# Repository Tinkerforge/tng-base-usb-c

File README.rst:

TNG Base USB C
==============

**This TNG module is currently in development.**

This repository contains the firmware source code and the hardware design
files. The documentation generator configs can be found at
https://github.com/Tinkerforge/generators

Repository Content
------------------

software/:
 * examples/: Examples for all supported languages
 * build/: Compiled files
 * src/: Source code of firmware
 * Makefile: Makefile to build project

hardware/:
 * Contains KiCad project files and additionally schematics as PDF

datasheets/:
 * Contains datasheets for sensors and complex ICs that are used

Hardware
--------

The hardware is designed with the open source EDA Suite KiCad
(http://www.kicad.org). Before you are able to open the files,
you have to install the Tinkerforge kicad-libraries
(https://github.com/Tinkerforge/kicad-libraries). You can either clone
them directly in hardware/ or clone them in a separate folder and
symlink them into hardware/
(ln -s kicad_path/kicad-libraries project_path/hardware). After that you
can open the .pro file in hardware/ with KiCad and from there view and
modify the schematics and the PCB layout.

Software
--------

If you want to do your own Brick/Bricklet firmware development we highly
recommend that you use our build environment setup script and read the
tutorial (https://www.tinkerforge.com/en/doc/Tutorials/Tutorial_Build_Environment/Tutorial.html).

To compile the C code we recommend you to install the newest GNU Arm Embedded
Toolchain (https://launchpad.net/gcc-arm-embedded/+download).
You also need to install bricklib2 (https://github.com/Tinkerforge/bricklib2).

You can either clone it directly in software/src/ or clone it in a
separate folder and symlink it into software/src/
(ln -s bricklib_path/bricklib2 project_path/software/src/). Finally make sure to
have CMake installed (http://www.cmake.org/cmake/resources/software.html).

After that you can build the firmware by invoking make in software/.
The firmware (.zbin) can then be found in software/build/ and uploaded
with brickv (click button "Flashing" on start screen).

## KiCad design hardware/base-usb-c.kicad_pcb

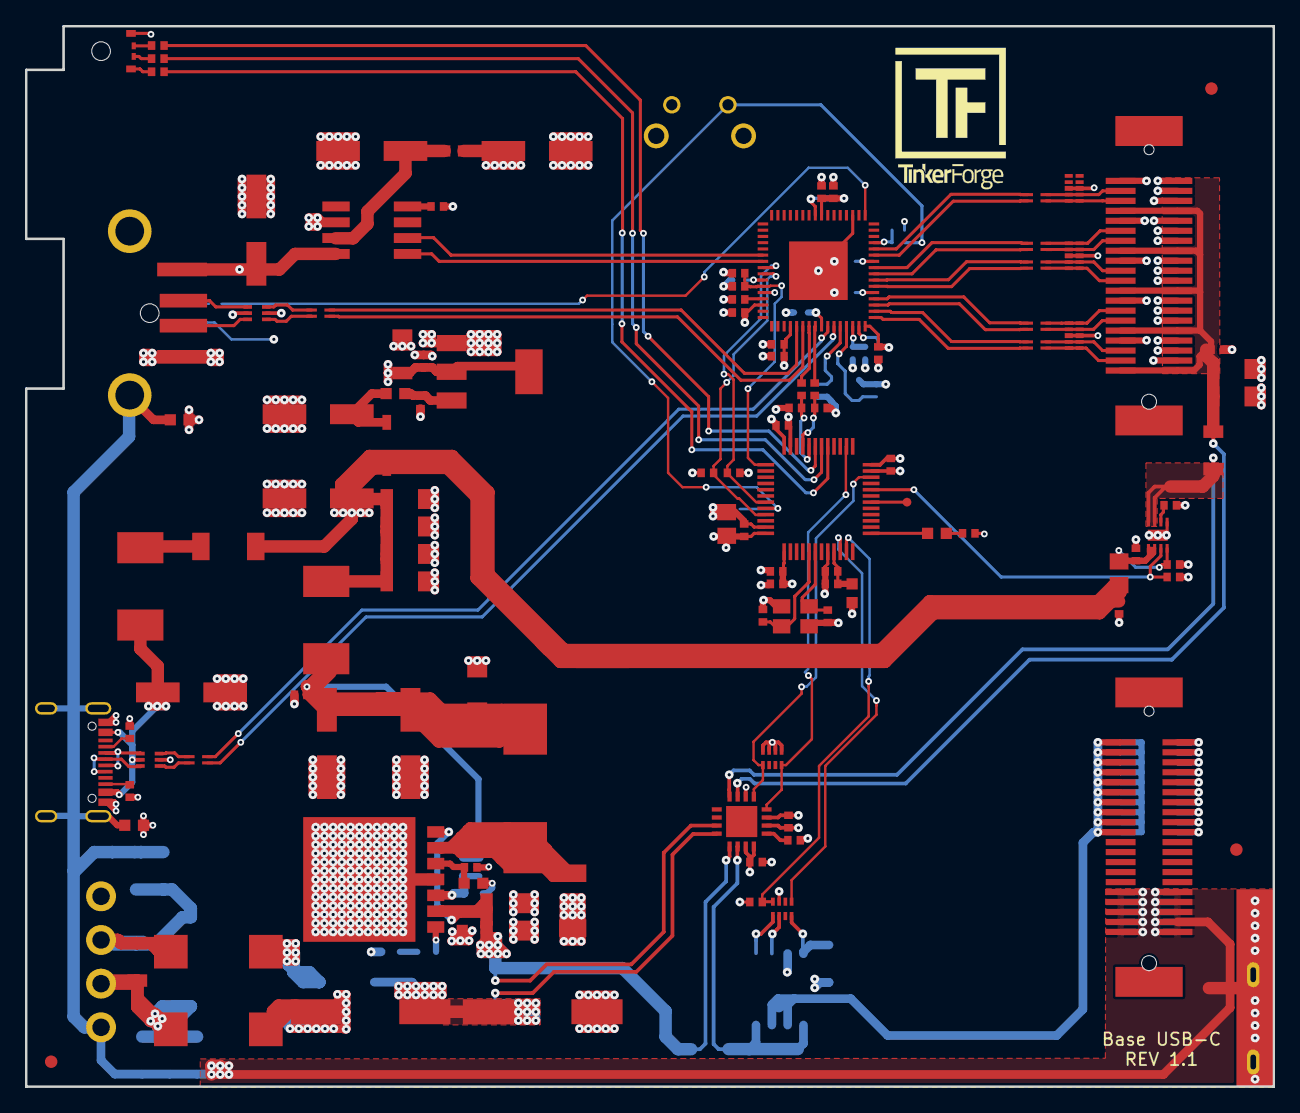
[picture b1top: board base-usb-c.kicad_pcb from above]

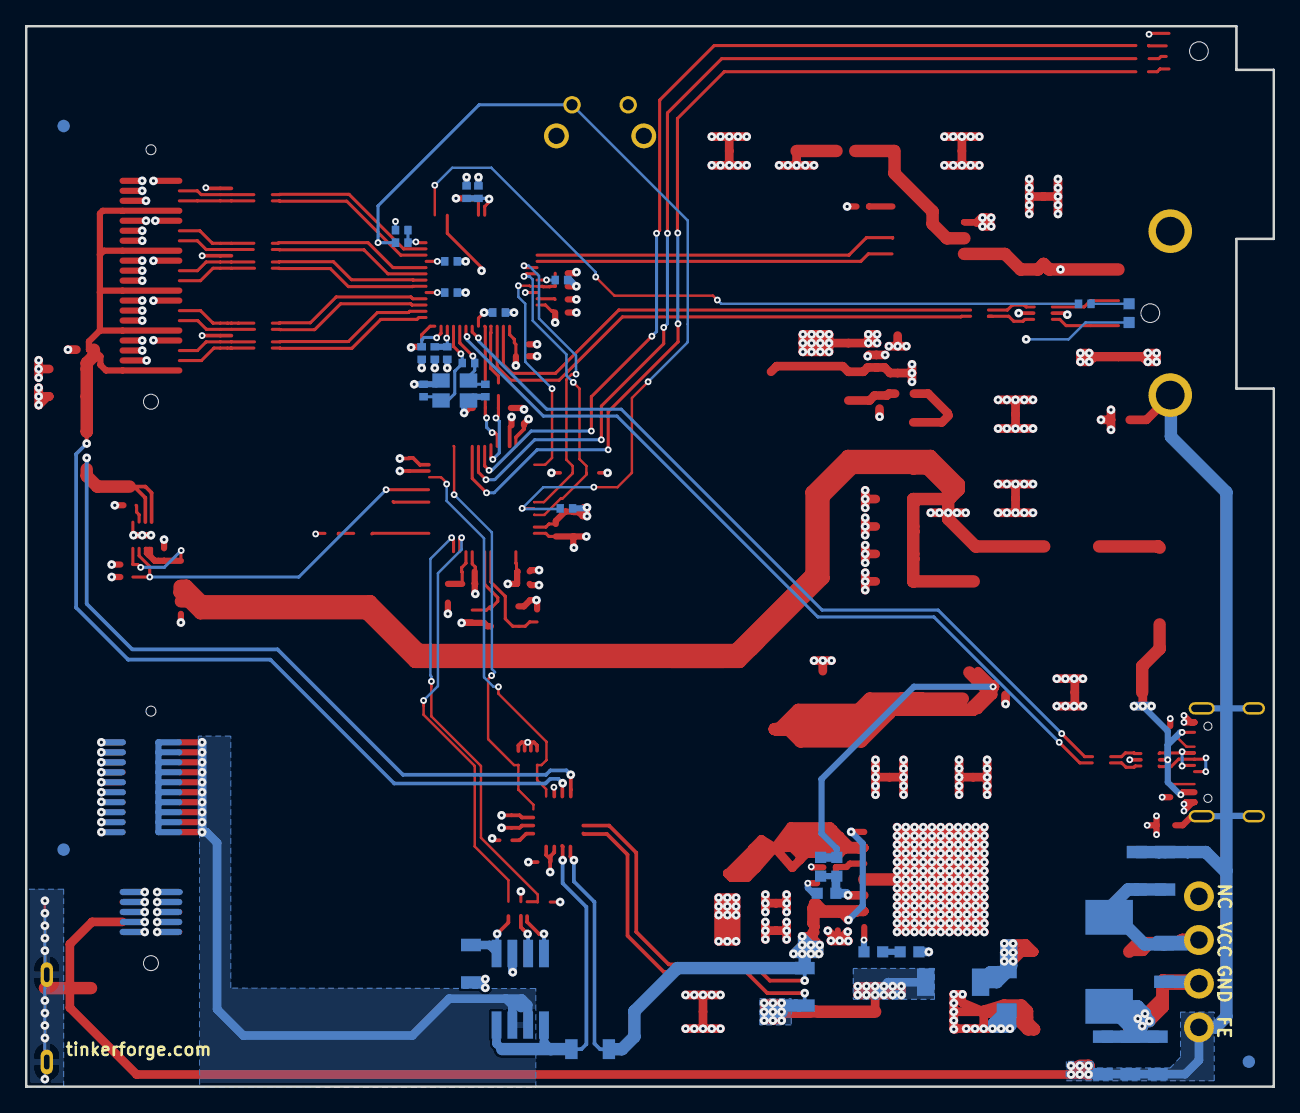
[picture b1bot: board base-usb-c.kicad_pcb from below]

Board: 4 copper layers, 100.0 x 85.0 mm, 157 parts (39 on the bottom side), 103 nets.

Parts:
C101, C102, C137, C138: 33pF; C0402F
C103, C105, C115, C119, C123, C124, C125, C126, C128, C134, C209, C226: 1uF; C0402F
C104, C106, C107, C110, C111, C112, C113, C114, C116, C118, C127, C129, C130, C131, C133, C214, C221, C222: 100nF; C0402F
C108, C109, C117, C141, C203, C216, C219, C220: 100uF; ELKO_63
C120, C140, C205: 100nF; C0603F
C121, C122: 47pF; C0402F
C132: DNP; C0402F
C135, C136, C201, C202, C215, C218, C223, C224, C225, C227: 10uF; C1206
C139: 10uF; C0805E
C204, C211: 10nF; C1206
C206, C207: 1nF 2kV; C1206
C208: 100pF; C0402F
C210: 4.7nF; C0603F
C212, C213: UWT1H221MNL1GS; ELKO_103
C217: DNP; C0603F
D101: LED green; LED-LP
D102: LED; D0603F
D201: 3.0SMI30CATR; SMC
D202, D205, D206: PMEG6045; SOD-128
D203: B0520LW-7-F; SOD-123
Fiducial_Mark: VAL**; Fiducial_Mark
Fiducial_Mark#2, Fiducial_Mark#3, Fiducial_Mark#4, Fiducial_Mark#5, Fiducial_Mark#6: VAL**; Fiducial_Mark
J101: USB-A; USB-A-SMT-8231
J102: USB-C; USB-C-2
J103: TNG-Power-TOP; TNG-40-TOP
J105: TNG-Data-TOP; TNG-40-TOP
L101, L201: INDUCTs; R0603F
L102, L103, L104, L105, L106, L107, L110: 744230900; WE-CNSW-0603
L108: FB; R0603F
L109: 742792040; R0805E
L111, L203: 10uH; SRP7030
L202: 22uH 74437368220; WE-LHMI
LED101: EASV3015RGBA0; LED-RGB-LP
P101: Debug; DEBUG_PAD
P102: PE; PE_Hook
P202: PWR IN; OQ_4P
R101, R105, R106, R107, R109, R111, R116, R117, R218: 10k; R0402F
R102: 100k; R0402F
R103: 1M; R0402F
R104, R108, R114, R121: 1k; R0402F
R110: 12k; R0402F
R112, R113: 22; R0402F
R115, R119: 0; R0402F
R118: 1k; R1206
R120: 56; R0402F
R122, R123: 5k1; R0402F
R204, R206, R207: VC1206K201R030; R1206
R208: 27k; R0603F
R209: 1M; R1206
R212: 20k; R0603F
R214: 47k; R0603F
R215: 8.2k; R0603F
R219, R220, R221: 0.02; R1206
RP102, RP201: 10k; 4X0402
SW101: BOOT; TACT-6MM-HOR
T201: 744272251; WE-SL5
U101: USB2517; QFN64-9x9mm-0.5mm_USB2517
U102: MIC2026-1YM; SO-8
U103, U108: 82400152; SOT563-SPEC
U104: STM32F070CBT6; LQFP48
U105, U106, U107: TPD4S010DQA
U110: TPS22975; WSON8-2x2
U112: VN7140AS; SO-8
U201: AZ1117EH; SOT-223
U203: BD90640HFP; BD906XX-C-HRP7
U204: PAC1933; QFN-16
X101: 24MHz; CRYSTAL_3225
X102: 8MHz; CRYSTAL_3225

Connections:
3V3: C110.1, C111.1, C112.1, C113.1, C114.1, C115.1, C116.1, C118.1, C119.1, C123.1, C127.1, C129.1, C130.1, C131.1, C139.1, C221.1, C222.1, C226.1, C227.1, D101.1, L108.1, LED101.1, R101.2, R102.2, R106.2, R111.2, R116.2, R117.2, R121.2, RP102.7, RP201.1, RP201.2, RP201.3, RP201.4, SW101.1, U101.5, U101.10, U101.24, U101.44, U101.46, U101.52, U101.57, U101.64, U104.1, U104.24, U104.36, U104.48, U201.2, U204.2, U204.6, U204.15, U204.16
5V_STACK_UP: C134.2, C135.2, C136.2, J105.7, J105.8, J105.15, J105.16, J105.23, J105.24, J105.31, J105.32, J105.39, J105.40, R221.2, U204.7
+5V: C108.1, C125.2, C218.1, C219.1, C223.1, C224.1, C225.1, D202.2, D203.1, L101.2, L109.1, L203.2
BOOT: R108.2, R114.2, SW101.2, U104.44
CTRL_USB_D+: C122.1, R112.2, U104.33
CTRL_USB_D-: C121.1, R113.2, U104.32
CUR1+: C212.1, C213.1, D205.2, R219.1, U204.12
CUR1-: C201.1, C202.1, C205.1, R219.2, R220.1, U203.2, U203.7, U204.11, U204.13
CUR2-: R220.2, U112.5, U112.8, U204.14
CUR3+: R221.1, U110.7, U110.8, U204.8
EXT_USB_D+: L102.1, U101.54
EXT_USB_D-: L102.4, U101.53
EXT_USB_D_F+: J101.3, U103.6
EXT_USB_D_F-: J101.2, U103.4
Earth: C120.1, C140.1, C206.2, C207.1, J101.SHD, J102.SHD, J103.31, J103.32, J103.33, J103.34, J103.35, J103.36, J103.37, J103.38, J103.39, J103.40, P102.1, P202.4, R206.2, R207.1, R209.1
GND: C101.2, C102.2, C103.2, C104.2, C105.2, C106.2, C107.2, C108.2, C109.2, C110.2, C111.2, C112.2, C113.2, C114.2, C115.2, C116.2, C117.2, C118.2, C119.2, C120.2, C121.2, C122.2, C123.2, C124.2, C125.1, C126.1, C127.2, C128.2, C129.2, C130.2, C131.2, C132.2, C133.2, C134.1, C135.1, C136.1, C137.1, C138.1, C139.2, C140.2, C141.2, C201.2, C202.2, C203.2, C205.2, C208.2, C209.2, C210.2, C211.2, C212.2, C213.2, C214.2, C215.2, C216.2, C218.2, C219.2, C220.2, C221.2, C222.2, C223.2, C224.2, C225.2, C226.2, C227.2, D206.1, J101.4, J102.6, J103.2, J103.4, J103.6, J103.8, J103.10, J103.12, J103.14, J103.16, J103.18, J103.20, J105.1, J105.2, J105.4, J105.6, J105.9, J105.10, J105.12, J105.14, J105.17, J105.18, J105.20, J105.22, J105.25, J105.26, J105.28, J105.30, J105.33, J105.34, J105.36, J105.38, R105.1, R107.2, R109.2, R110.1, R114.1, R118.1, R122.1, R123.1, R208.1, R215.1, R218.2, T201.3, U101.19, U101.EXP, U102.6, U103.2, U104.8, U104.23, U104.35, U104.47, U105.3, U105.8, U106.3, U106.8, U107.3, U107.8, U108.2, U110.5, U110.EXP, U112.3, U201.1, U203.4, U203.EXP, U204.3, X101.3, X102.3
LEDB: R120.1, U104.31
LEDG: R119.1, U104.30
LEDR: R115.1, U104.29
unnamed: C101.1, R103.2, U101.61, X101.1
unnamed: C102.1, R103.1, U101.60, X101.2
unnamed: C103.1, C104.1, U101.25
unnamed: C105.1, C106.1, U101.62
unnamed: C109.1, L101.1, U102.7
unnamed: C124.1, C133.1, L108.2, U104.9
unnamed: C126.2, C128.1, L109.2, U110.1, U110.2, U110.4
unnamed: C132.1, U110.6
unnamed: C137.2, U104.5, X102.2
unnamed: C138.2, U104.6, X102.1
unnamed: C141.1, J102.1, L111.2, U108.5
unnamed: C203.1, D203.2, L201.1
unnamed: C204.1, C206.1, D201.1, P202.2, R204.1, R206.1, T201.1
unnamed: C204.2, C207.2, D201.2, P202.3, R204.2, R207.2, R209.2, T201.2
unnamed: C208.1, R208.2, U203.5
unnamed: C209.1, L201.2, U201.3
unnamed: C210.1, R212.1
unnamed: C211.1, D205.1, T201.4
unnamed: C214.1, C215.1, C216.1, C217.1, C220.1, L202.2, L203.1, R214.2
unnamed: C217.2, R214.1, R215.2, U203.3
unnamed: D101.2, R104.2
unnamed: D102.1, R121.1
unnamed: D102.2, U104.13
unnamed: D206.2, L202.1, U203.6
unnamed: J102.2, U108.4
unnamed: J102.3, U108.6
unnamed: J102.4, R123.2
unnamed: J102.5, R122.2
unnamed: L102.2, U103.1
unnamed: L102.3, U103.3
unnamed: L110.2, U108.1
unnamed: L110.3, U108.3
unnamed: LED101.2, R120.2
unnamed: LED101.3, R119.2
unnamed: LED101.4, R115.2
unnamed: P101.1, U104.18
unnamed: R101.1, U101.45
unnamed: R104.1, U101.17
unnamed: R105.2, U102.4
unnamed: R107.1, U101.42
unnamed: R108.1, R109.1, U101.13
unnamed: R110.2, U101.63
unnamed: R112.1, U101.56
unnamed: R113.1, U101.55
unnamed: R118.2, RP102.4, U112.4
unnamed: R212.2, U203.1
unnamed: R218.1, U204.1
unnamed: RP102.1, U112.1
unnamed: RP102.2, U112.2
unnamed: U101.38, U102.2
unnamed: U101.39, U102.1
PAC_SCL: RP201.8, U104.26, U204.4
PAC_SDA: RP201.5, U104.22, U204.5
STACKPWR: J103.1, J103.3, J103.5, J103.7, J103.9, J103.11, J103.13, J103.15, J103.17, J103.19, U112.6, U112.7
STACK_USB_D0+: L103.1, U101.12
STACK_USB_D0-: L103.4, U101.11
STACK_USB_D0_F+: J105.3, L103.2, U105.4, U105.7
STACK_USB_D0_F-: J105.5, L103.3, U105.5, U105.6
STACK_USB_D1+: L104.1, U101.9
STACK_USB_D1-: L104.4, U101.8
STACK_USB_D1_F+: J105.11, L104.2, U106.5, U106.6
STACK_USB_D1_F-: J105.13, L104.3, U106.4, U106.7
STACK_USB_D2+: L105.1, U101.7
STACK_USB_D2-: L105.4, U101.6
STACK_USB_D2_F+: J105.19, L105.2, U106.2, U106.9
STACK_USB_D2_F-: J105.21, L105.3, U106.1, U106.10
STACK_USB_D3+: L106.1, U101.4
STACK_USB_D3-: L106.4, U101.3
STACK_USB_D3_F+: J105.27, L106.2, U107.5, U107.6
STACK_USB_D3_F-: J105.29, L106.3, U107.4, U107.7
STACK_USB_D4+: L107.1, U101.2
STACK_USB_D4-: L107.4, U101.1
STACK_USB_D4_F+: J105.35, L107.2, U107.2, U107.9
STACK_USB_D4_F-: J105.37, L107.3, U107.1, U107.10
SW_5_ENABLE: R116.1, U104.20, U110.3
SW_24_CUR: RP102.5, U104.10
SW_24_ENABLE: R117.1, RP102.8, U104.11
UP_USB_D+: L110.1, U101.59
UP_USB_D-: L110.4, U101.58
USB-PWR: C117.1, J101.1, U102.8, U103.5
USB_RESET: C107.1, R102.1, U101.43, U104.37
USB_SMB_CLK: R111.1, U101.41, U104.45
USB_SMB_DATA: R106.1, U101.40, U104.43
VBUS: D202.1, L111.1

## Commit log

2020-07-02 checkin
2020-07-27 Add autogenerated TNG Base USB C firmware stub
2020-08-25 version 1.1
    * fix usb-c cc resistors
2020-09-04 add version 1.1
    fix usb c
    fix footprints
2020-09-07 fix values
2020-09-07 fix value
2020-09-07 small changes
2020-09-07 fix footprint
2020-09-08 all footprints updated
2020-09-09 fix outline
2020-09-10 fix usb positon, fix 3d
2020-11-19 Add initial stub implementation of base-usb-c
2021-10-25 Update KiCad link
    https://www.kicad.org/blog/2021/10/Avoid-links-to-former-kicad-domain/

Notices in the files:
hardware/base-usb-c.kicad_pcb:
Licensed under CERN OHL v.1.1
Copyright (©) 2020, B.Nordmeyer
Copyright Tinkerforge GmbH 2020.
This documentation describes Open Hardware and is licensed under the
CERN OHL v. 1.1.
